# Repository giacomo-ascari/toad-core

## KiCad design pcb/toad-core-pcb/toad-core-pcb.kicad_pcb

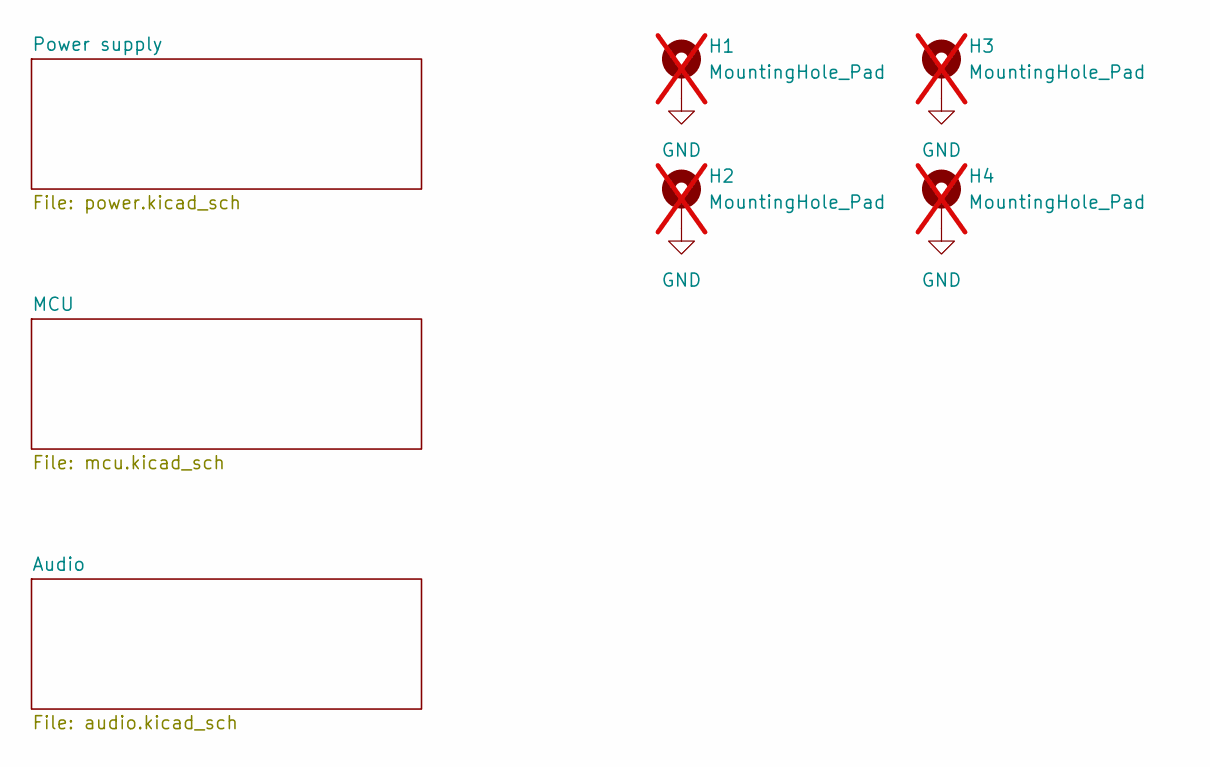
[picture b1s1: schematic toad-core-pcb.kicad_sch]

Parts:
H1, H2, H3, H4: MountingHole_Pad; MountingHole_3.2mm_M3_ISO14580_Pad; not fitted

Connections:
GND: H1.1 (1_1), H2.1 (1_1), H3.1 (1_1), H4.1 (1_1); also elsewhere on the board

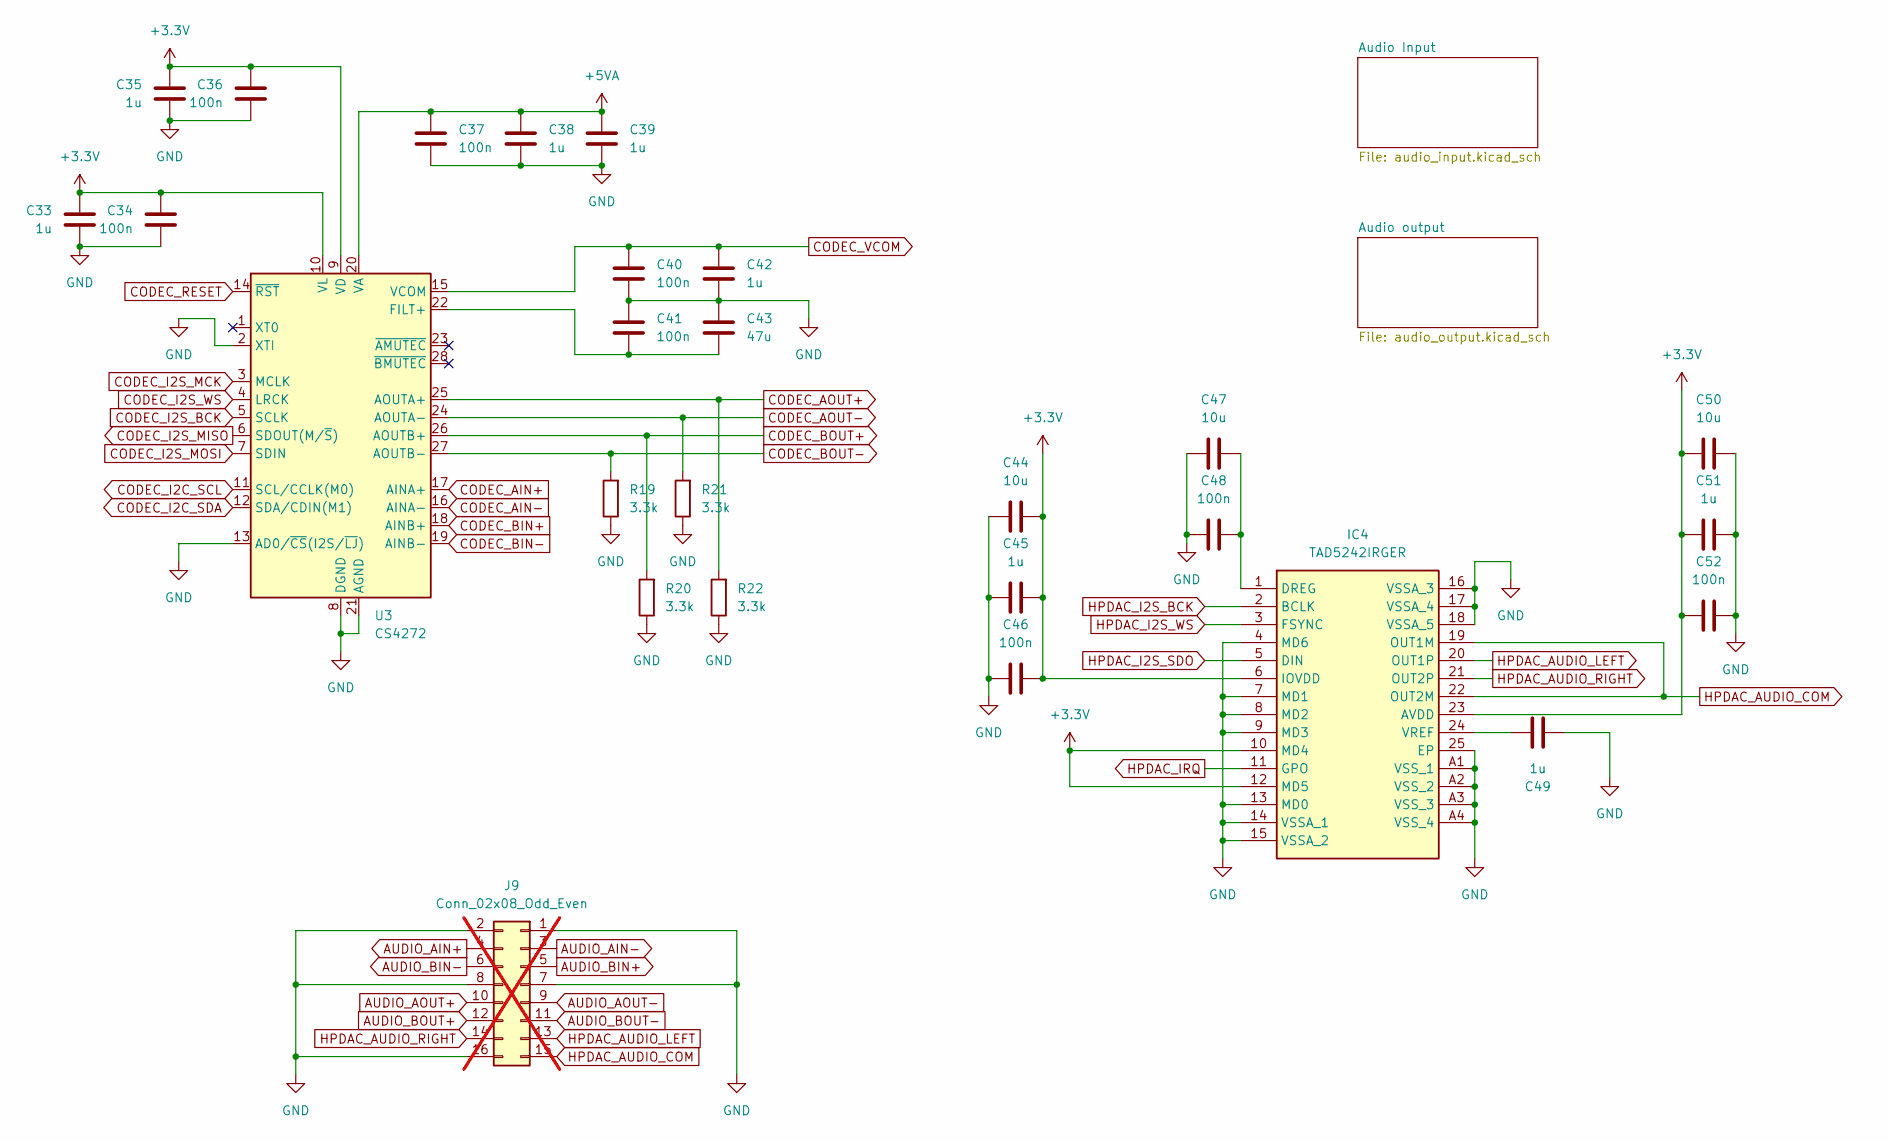
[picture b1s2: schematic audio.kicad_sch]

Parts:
C33, C35, C38, C39, C42, C45, C49, C51: 1u; C_0603_1608Metric; JLCPCB Part # C15849
C34, C36, C37, C40, C41, C46, C48, C52: 100n; C_0603_1608Metric; JLCPCB Part # C14663
C43: 47u; C_0805_2012Metric; JLCPCB Part # C16780
C44, C47, C50: 10u; C_0805_2012Metric; JLCPCB Part # C440198
IC4: TAD5242IRGER; Manufacturer_Part_Number TAD5242IRGER; Mouser Part Number 595-TAD5242IRGER
J9: Conn_02x08_Odd_Even; PinHeader_2x08_P2.54mm_Vertical; not fitted
R19, R20, R21, R22: 3.3k; R_0603_1608Metric; JLCPCB Part # C22978
U3: CS4272; TSSOP-28_4.4x9.7mm_P0.65mm; JLCPCB Part # C2151111

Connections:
+3.3V: C33.1, C34.1, C35.1, C36.1, C44.1, C45.1, C46.1, C50.1, C51.1, C52.1, IC4.6 (IOVDD), IC4.10 (MD4), IC4.12 (MD5), IC4.23 (AVDD), U3.9 (VD), U3.10 (VL); also elsewhere on the board
+5VA: C37.1, C38.1, C39.1, U3.20 (VA); also elsewhere on the board
AUDIO_AIN+: J9.4; also elsewhere on the board
AUDIO_AIN-: J9.3; also elsewhere on the board
AUDIO_AOUT+: J9.10; also elsewhere on the board
AUDIO_AOUT-: J9.9; also elsewhere on the board
AUDIO_BIN+: J9.5; also elsewhere on the board
AUDIO_BIN-: J9.6; also elsewhere on the board
AUDIO_BOUT+: J9.12; also elsewhere on the board
AUDIO_BOUT-: J9.11; also elsewhere on the board
CODEC_AIN+: U3.17 (AINA+); also elsewhere on the board
CODEC_AIN-: U3.16 (AINA-); also elsewhere on the board
CODEC_AOUT+: R22.2, U3.25 (AOUTA+); also elsewhere on the board
CODEC_AOUT-: R21.2, U3.24 (AOUTA-); also elsewhere on the board
CODEC_BIN+: U3.18 (AINB+); also elsewhere on the board
CODEC_BIN-: U3.19 (AINB-); also elsewhere on the board
CODEC_BOUT+: R20.2, U3.26 (AOUTB+); also elsewhere on the board
CODEC_BOUT-: R19.2, U3.27 (AOUTB-); also elsewhere on the board
CODEC_I2C_SCL: U3.11 (SCL/CCLK(M0)); also elsewhere on the board
CODEC_I2C_SDA: U3.12 (SDA/CDIN(M1)); also elsewhere on the board
CODEC_I2S_BCK: U3.5 (SCLK); also elsewhere on the board
CODEC_I2S_MCK: U3.3 (MCLK); also elsewhere on the board
CODEC_I2S_MISO: U3.6 (SDOUT(M/~S)); also elsewhere on the board
CODEC_I2S_MOSI: U3.7 (SDIN); also elsewhere on the board
CODEC_I2S_WS: U3.4 (LRCK); also elsewhere on the board
CODEC_RESET: U3.14 (~RST); also elsewhere on the board
CODEC_VCOM: C40.1, C42.1, U3.15 (VCOM); also elsewhere on the board
GND: C33.2, C34.2, C35.2, C36.2, C37.2, C38.2, C39.2, C40.2, C41.1, C42.2, C43.1, C44.2, C45.2, C46.2, C47.2, C48.2, C49.1, C50.2, C51.2, C52.2, IC4.4 (MD6), IC4.7 (MD1), IC4.8 (MD2), IC4.9 (MD3), IC4.13 (MD0), IC4.14 (VSSA_1), IC4.15 (VSSA_2), IC4.16 (VSSA_3), IC4.17 (VSSA_4), IC4.18 (VSSA_5), IC4.25 (EP), IC4.A1 (VSS_1), IC4.A2 (VSS_2), IC4.A3 (VSS_3), IC4.A4 (VSS_4), J9.1, J9.2, J9.7, J9.8, J9.16, R19.1, R20.1, R21.1, R22.1, U3.2 (XTI), U3.8 (DGND), U3.13 (AD0/~CS(I2S/~LJ)), U3.21 (AGND); also elsewhere on the board
HPDAC_AUDIO_COM: IC4.19 (OUT1M), IC4.22 (OUT2M), J9.15
HPDAC_AUDIO_LEFT: IC4.20 (OUT1P), J9.13
HPDAC_AUDIO_RIGHT: IC4.21 (OUT2P), J9.14
HPDAC_I2S_BCK: IC4.2 (BCLK); also elsewhere on the board
HPDAC_I2S_SDO: IC4.5 (DIN); also elsewhere on the board
HPDAC_I2S_WS: IC4.3 (FSYNC); also elsewhere on the board
HPDAC_IRQ: IC4.11 (GPO); also elsewhere on the board
unnamed: C47.1, C48.1, IC4.1 (DREG)
unnamed: C49.2, IC4.24 (VREF)
unnamed: C41.2, C43.2, U3.22 (FILT+)

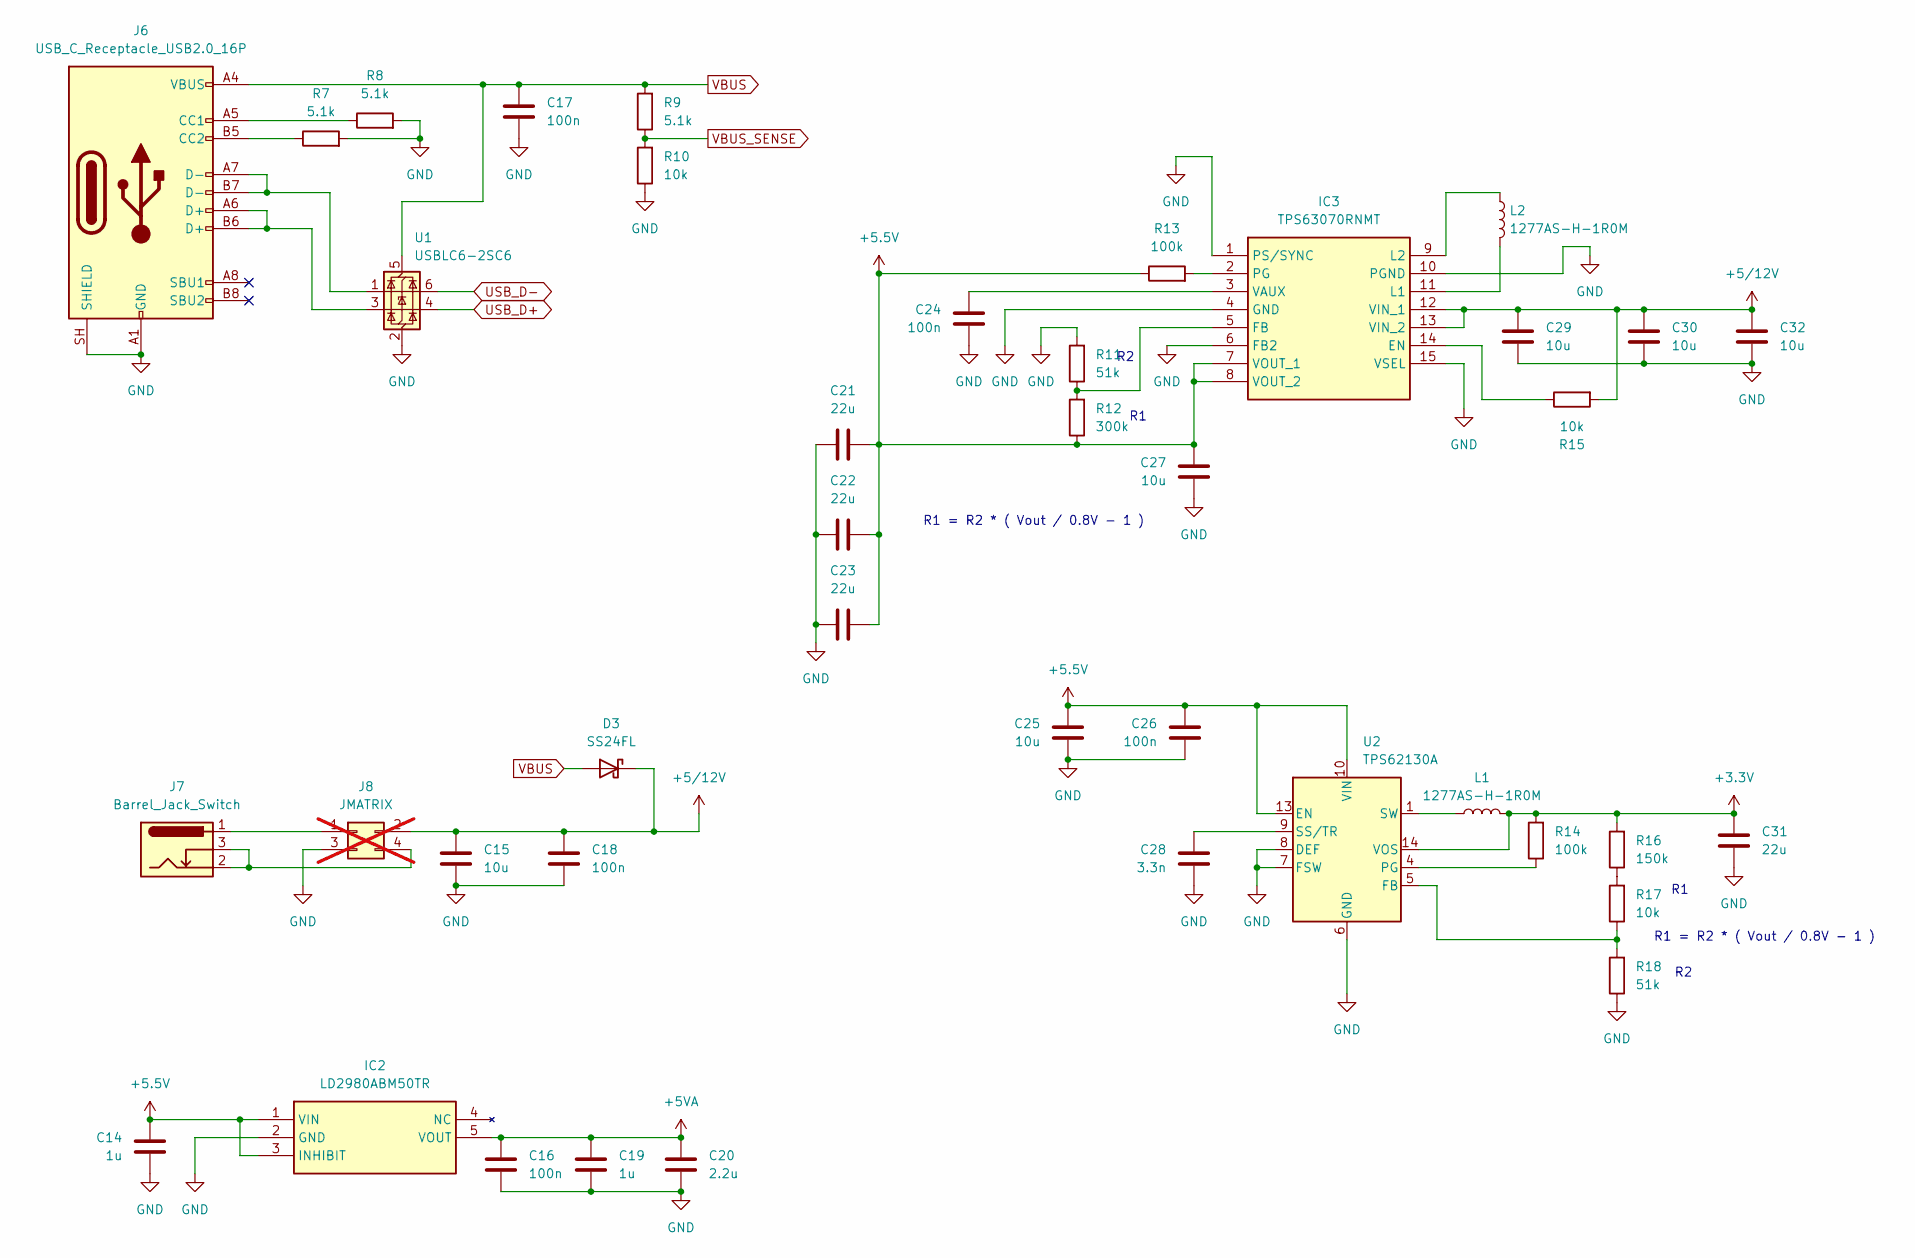
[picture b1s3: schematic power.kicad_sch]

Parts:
C14, C19: 1u; C_0603_1608Metric; JLCPCB Part # C15849
C15, C25, C30, C32: 10u; C_0805_2012Metric; JLCPCB Part # C440198
C16, C17, C18, C24, C26: 100n; C_0603_1608Metric; JLCPCB Part # C14663
C20: 2.2u; C_0603_1608Metric; JLCPCB Part # C23630
C21, C22, C23, C31: 22u; C_0805_2012Metric; JLCPCB Part # C45783
C27, C29: 10u; C_0603_1608Metric; JLCPCB Part # C96446
C28: 3.3n; C_0603_1608Metric; JLCPCB Part # C1613
D3: SS24FL; D_SOD-123F; JLCPCB Part # C894433
IC2: LD2980ABM50TR; SOT95P280X145-5N; Manufacturer_Part_Number LD2980ABM50TR; Mouser Part Number 511-LD2980ABM50
IC3: TPS63070RNMT; TPS630701RNMR; Manufacturer_Part_Number TPS63070RNMT; Mouser Part Number 595-TPS63070RNMT
J6: USB_C_Receptacle_USB2.0_16P; USB_C_Receptacle_GCT_USB4105-xx-A_16P_TopMnt_Horizontal; JLCPCB Part # C3020560
J7: Barrel_Jack_Switch; BarrelJack_Wuerth_6941xx301002; JLCPCB Part # C5441017
J8: JMATRIX; PinHeader_2x02_P2.54mm_Vertical; not fitted
L1, L2: 1277AS-H-1R0M; L_1210_3225Metric; JLCPCB Part # C237284
R7, R8, R9: 5.1k; R_0603_1608Metric; JLCPCB Part # C23186
R10, R15, R17: 10k; R_0603_1608Metric; JLCPCB Part # C25804
R11, R18: 51k; R_0603_1608Metric; JLCPCB Part # C23196
R12: 300k; R_0603_1608Metric; JLCPCB Part # C23024
R13, R14: 100k; R_0603_1608Metric; JLCPCB Part # C25803
R16: 150k; R_0603_1608Metric; JLCPCB Part # C22807
U1: USBLC6-2SC6; SOT-23-6; JLCPCB Part # C7519
U2: TPS62130A; VQFN-16-1EP_3x3mm_P0.5mm_EP1.68x1.68mm_ThermalVias; JLCPCB Part # C2070623

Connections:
+3.3V: C31.1, L1.2, R14.2, R16.2, U2.14 (VOS); also elsewhere on the board
+5.5V: C14.1, C21.2, C22.2, C23.2, C25.1, C26.1, C27.1, IC2.1 (VIN), IC2.3 (INHIBIT), IC3.7 (VOUT_1), IC3.8 (VOUT_2), R12.1, R13.1, U2.10 (VIN), U2.11 (VIN), U2.12 (VIN), U2.13 (EN)
+5VA: C16.1, C19.1, C20.1, IC2.5 (VOUT); also elsewhere on the board
+5/12V: C15.1, C18.1, C29.1, C30.1, C32.1, D3.1 (K), IC3.12 (VIN_1), IC3.13 (VIN_2), J8.2, R15.2
GND: C14.2, C15.2, C16.2, C17.2, C18.2, C19.2, C20.2, C21.1, C22.1, C23.1, C24.2, C25.2, C26.2, C27.2, C28.2, C29.2, C30.2, C31.2, C32.2, IC2.2 (GND), IC3.1 (PS/SYNC), IC3.4 (GND), IC3.6 (FB2), IC3.10 (PGND), IC3.15 (VSEL), J6.A1 (GND), J6.A12 (GND), J6.B1 (GND), J6.B12 (GND), J6.SH (SHIELD), J8.3, R7.2, R8.2, R10.1, R11.2, R18.1, U1.2 (GND), U2.6 (GND), U2.7 (FSW), U2.8 (DEF), U2.15 (GND), U2.16 (GND), U2.17 (GND); also elsewhere on the board
unnamed: IC3.14 (EN), R15.1
unnamed: IC3.5 (FB), R11.1, R12.2
unnamed: IC3.11 (L1), L2.2
unnamed: IC3.9 (L2), L2.1
unnamed: IC3.2 (PG), R13.2
unnamed: C24.1, IC3.3 (VAUX)
unnamed: J6.A5 (CC1), R8.1
unnamed: J6.B5 (CC2), R7.1
unnamed: J6.A6 (D+), J6.B6 (D+), U1.3 (I/O2)
unnamed: J6.A7 (D-), J6.B7 (D-), U1.1 (I/O1)
unnamed: J7.1, J8.1
unnamed: J7.2, J7.3, J8.4
unnamed: L1.1, U2.1 (SW), U2.2 (SW), U2.3 (SW)
unnamed: R16.1, R17.2
unnamed: R17.1, R18.2, U2.5 (FB)
unnamed: R14.1, U2.4 (PG)
unnamed: C28.1, U2.9 (SS/TR)
USB_D+: U1.4 (I/O2); also elsewhere on the board
USB_D-: U1.6 (I/O1); also elsewhere on the board
VBUS: C17.1, D3.2 (A), J6.A4 (VBUS), J6.A9 (VBUS), J6.B4 (VBUS), J6.B9 (VBUS), R9.2, U1.5 (VBUS)
VBUS_SENSE: R9.1, R10.2; also elsewhere on the board

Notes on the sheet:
R1 = R2 * ( Vout / 0.8V - 1 )

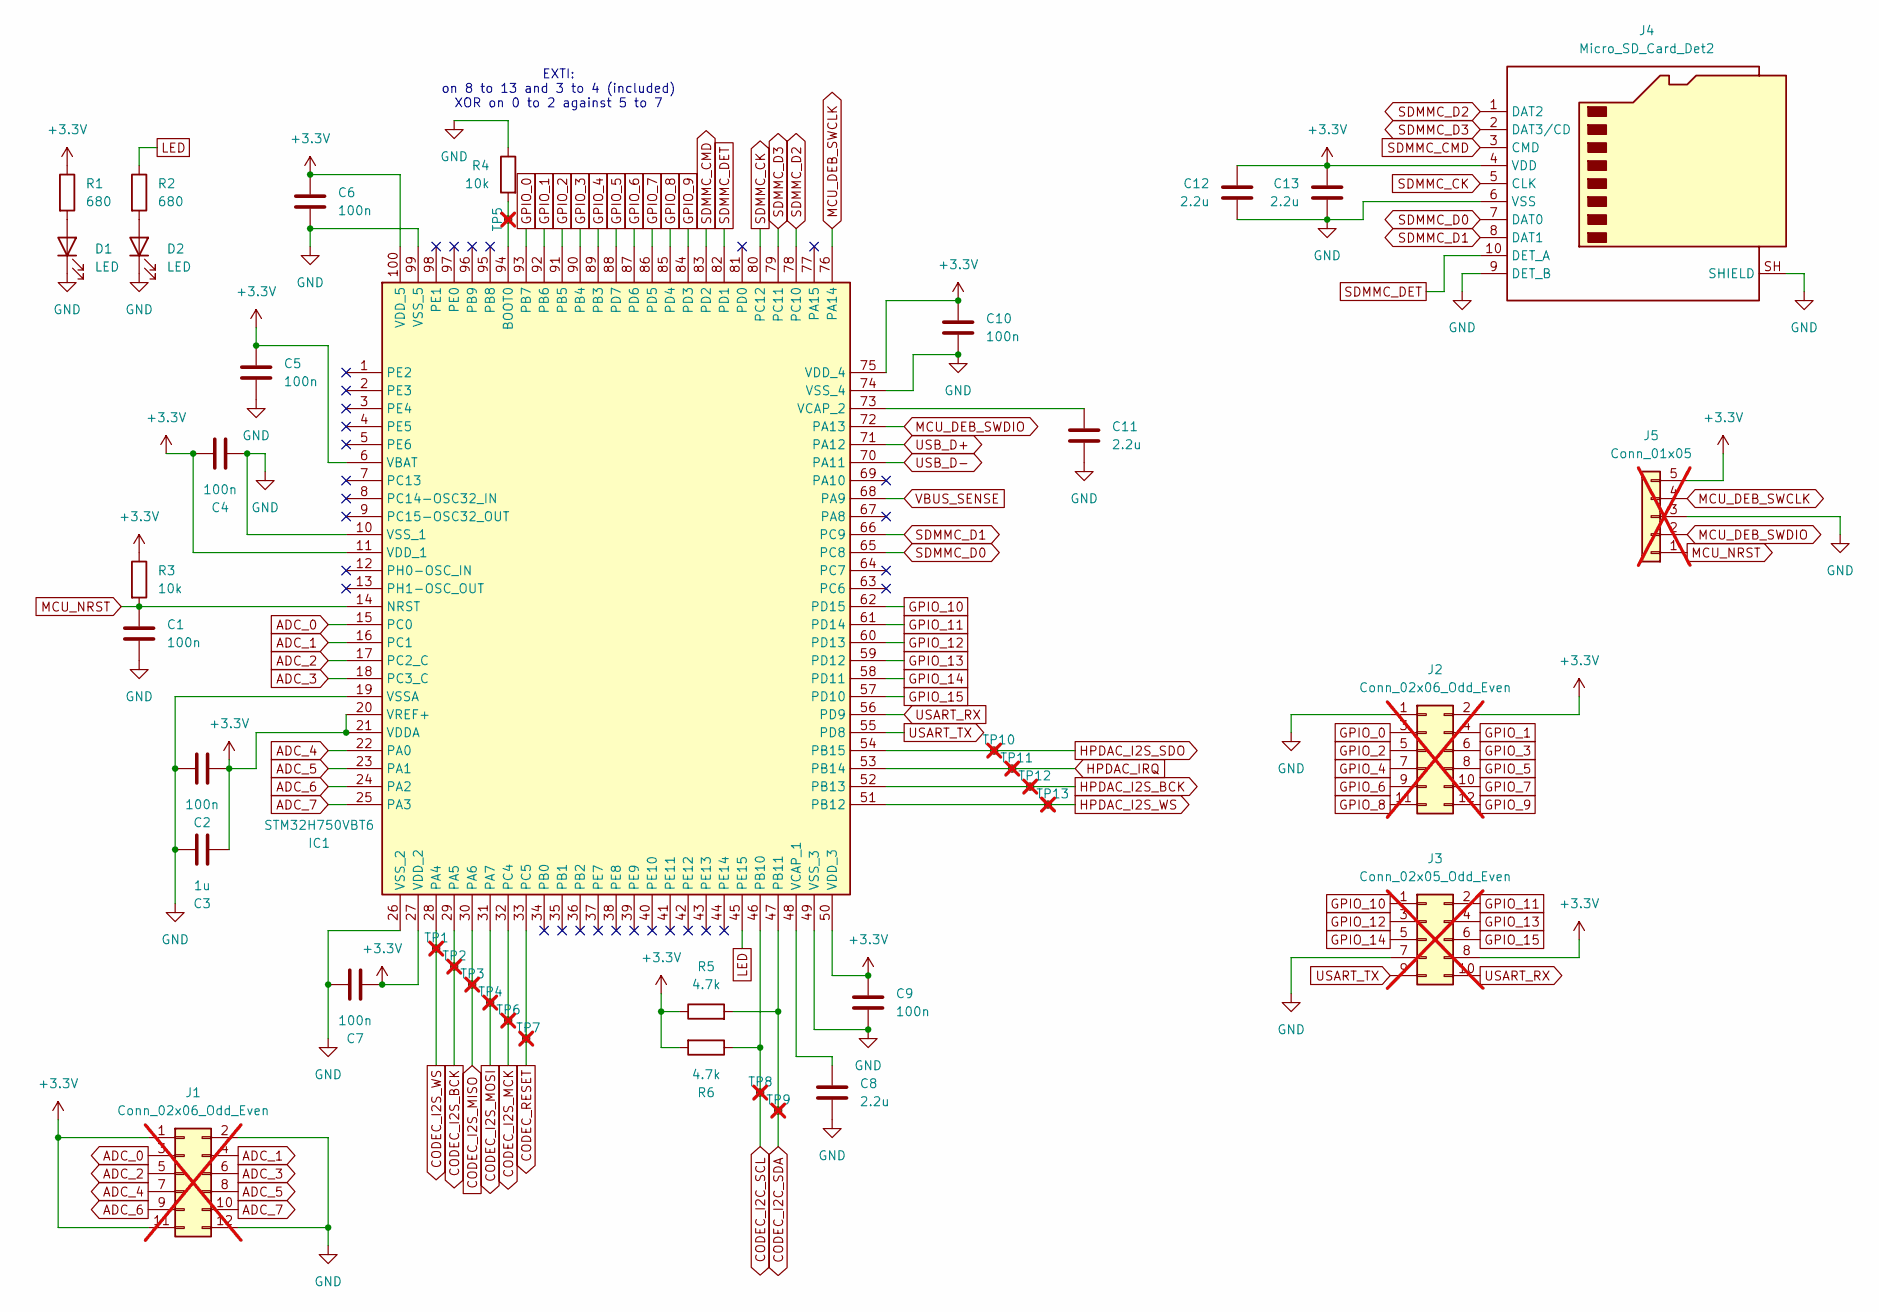
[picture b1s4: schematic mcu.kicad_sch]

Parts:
C1, C2, C4, C5, C6, C7, C9, C10: 100n; C_0603_1608Metric; JLCPCB Part # C14663
C3: 1u; C_0603_1608Metric; JLCPCB Part # C15849
C8, C11, C12, C13: 2.2u; C_0603_1608Metric; JLCPCB Part # C23630
D1, D2: LED; LED_0603_1608Metric; JLCPCB Part # C2286
IC1: STM32H750VBT6; QFP50P1600X1600X160-100N; Manufacturer_Part_Number STM32H750VBT6; Mouser Part Number 511-STM32H750VBT6
J1, J2: Conn_02x06_Odd_Even; PinHeader_2x06_P2.54mm_Vertical; not fitted
J3: Conn_02x05_Odd_Even; PinHeader_2x05_P2.54mm_Vertical; not fitted
J4: Micro_SD_Card_Det2; microSD_HC_Molex_104031-0811; JLCPCB Part # C585350
J5: Conn_01x05; JST_PH_B5B-PH-K_1x05_P2.00mm_Vertical; not fitted
R1, R2: 680; R_0603_1608Metric; JLCPCB Part # C23228
R3, R4: 10k; R_0603_1608Metric; JLCPCB Part # C25804
R5, R6: 4.7k; R_0603_1608Metric; JLCPCB Part # C23162
TP1, TP2, TP3, TP4, TP5, TP6, TP7, TP8, TP9, TP10, TP11, TP12, TP13: TestPoint_Small; custom_d0.6; not fitted

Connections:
+3.3V: C2.1, C3.1, C4.2, C5.1, C6.1, C7.1, C9.1, C10.1, C12.1, C13.1, IC1.6 (VBAT), IC1.11 (VDD_1), IC1.20 (VREF+), IC1.21 (VDDA), IC1.27 (VDD_2), IC1.50 (VDD_3), IC1.75 (VDD_4), IC1.100 (VDD_5), J1.1, J1.11, J2.2, J3.8, J4.4 (VDD), J5.5, R1.1, R3.1, R5.1, R6.2; also elsewhere on the board
ADC_0: IC1.15 (PC0), J1.3
ADC_1: IC1.16 (PC1), J1.4
ADC_2: IC1.17 (PC2_C), J1.5
ADC_3: IC1.18 (PC3_C), J1.6
ADC_4: IC1.22 (PA0), J1.7
ADC_5: IC1.23 (PA1), J1.8
ADC_6: IC1.24 (PA2), J1.9
ADC_7: IC1.25 (PA3), J1.10
CODEC_I2C_SCL: IC1.46 (PB10), R6.1, TP8.1 (1_1); also elsewhere on the board
CODEC_I2C_SDA: IC1.47 (PB11), R5.2, TP9.1 (1_1); also elsewhere on the board
CODEC_I2S_BCK: IC1.29 (PA5), TP2.1 (1_1); also elsewhere on the board
CODEC_I2S_MCK: IC1.32 (PC4), TP6.1 (1_1); also elsewhere on the board
CODEC_I2S_MISO: IC1.30 (PA6), TP3.1 (1_1); also elsewhere on the board
CODEC_I2S_MOSI: IC1.31 (PA7), TP4.1 (1_1); also elsewhere on the board
CODEC_I2S_WS: IC1.28 (PA4), TP1.1 (1_1); also elsewhere on the board
CODEC_RESET: IC1.33 (PC5), TP7.1 (1_1); also elsewhere on the board
GND: C1.2, C2.2, C3.2, C4.1, C5.2, C6.2, C7.2, C8.2, C9.2, C10.2, C11.2, C12.2, C13.2, D1.1 (K), D2.1 (K), IC1.10 (VSS_1), IC1.19 (VSSA), IC1.26 (VSS_2), IC1.49 (VSS_3), IC1.74 (VSS_4), IC1.99 (VSS_5), J1.2, J1.12, J2.1, J3.7, J4.6 (VSS), J4.9 (DET_B), J4.SH (SHIELD), J5.3, R4.1; also elsewhere on the board
GPIO_0: IC1.93 (PB7), J2.3
GPIO_1: IC1.92 (PB6), J2.4
GPIO_2: IC1.91 (PB5), J2.5
GPIO_3: IC1.90 (PB4), J2.6
GPIO_4: IC1.89 (PB3), J2.7
GPIO_5: IC1.88 (PD7), J2.8
GPIO_6: IC1.87 (PD6), J2.9
GPIO_7: IC1.86 (PD5), J2.10
GPIO_8: IC1.85 (PD4), J2.11
GPIO_9: IC1.84 (PD3), J2.12
GPIO_10: IC1.62 (PD15), J3.1
GPIO_11: IC1.61 (PD14), J3.2
GPIO_12: IC1.60 (PD13), J3.3
GPIO_13: IC1.59 (PD12), J3.4
GPIO_14: IC1.58 (PD11), J3.5
GPIO_15: IC1.57 (PD10), J3.6
HPDAC_I2S_BCK: IC1.52 (PB13), TP12.1 (1_1); also elsewhere on the board
HPDAC_I2S_SDO: IC1.54 (PB15), TP10.1 (1_1); also elsewhere on the board
HPDAC_I2S_WS: IC1.51 (PB12), TP13.1 (1_1); also elsewhere on the board
HPDAC_IRQ: IC1.53 (PB14), TP11.1 (1_1); also elsewhere on the board
LED: IC1.45 (PE15), R2.1
MCU_DEB_SWCLK: IC1.76 (PA14), J5.4
MCU_DEB_SWDIO: IC1.72 (PA13), J5.2
MCU_NRST: C1.1, IC1.14 (NRST), J5.1, R3.2
unnamed: D1.2 (A), R1.2
unnamed: D2.2 (A), R2.2
unnamed: IC1.94 (BOOT0), R4.2, TP5.1 (1_1)
unnamed: C8.1, IC1.48 (VCAP_1)
unnamed: C11.1, IC1.73 (VCAP_2)
SDMMC_CK: IC1.80 (PC12), J4.5 (CLK)
SDMMC_CMD: IC1.83 (PD2), J4.3 (CMD)
SDMMC_D0: IC1.65 (PC8), J4.7 (DAT0)
SDMMC_D1: IC1.66 (PC9), J4.8 (DAT1)
SDMMC_D2: IC1.78 (PC10), J4.1 (DAT2)
SDMMC_D3: IC1.79 (PC11), J4.2 (DAT3/CD)
SDMMC_DET: IC1.82 (PD1), J4.10 (DET_A)
USART_RX: IC1.56 (PD9), J3.10
USART_TX: IC1.55 (PD8), J3.9
USB_D+: IC1.71 (PA12); also elsewhere on the board
USB_D-: IC1.70 (PA11); also elsewhere on the board
VBUS_SENSE: IC1.68 (PA9); also elsewhere on the board

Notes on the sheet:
EXTI: on 8 to 13 and 3 to 4 (included) XOR on 0 to 2 against 5 to 7

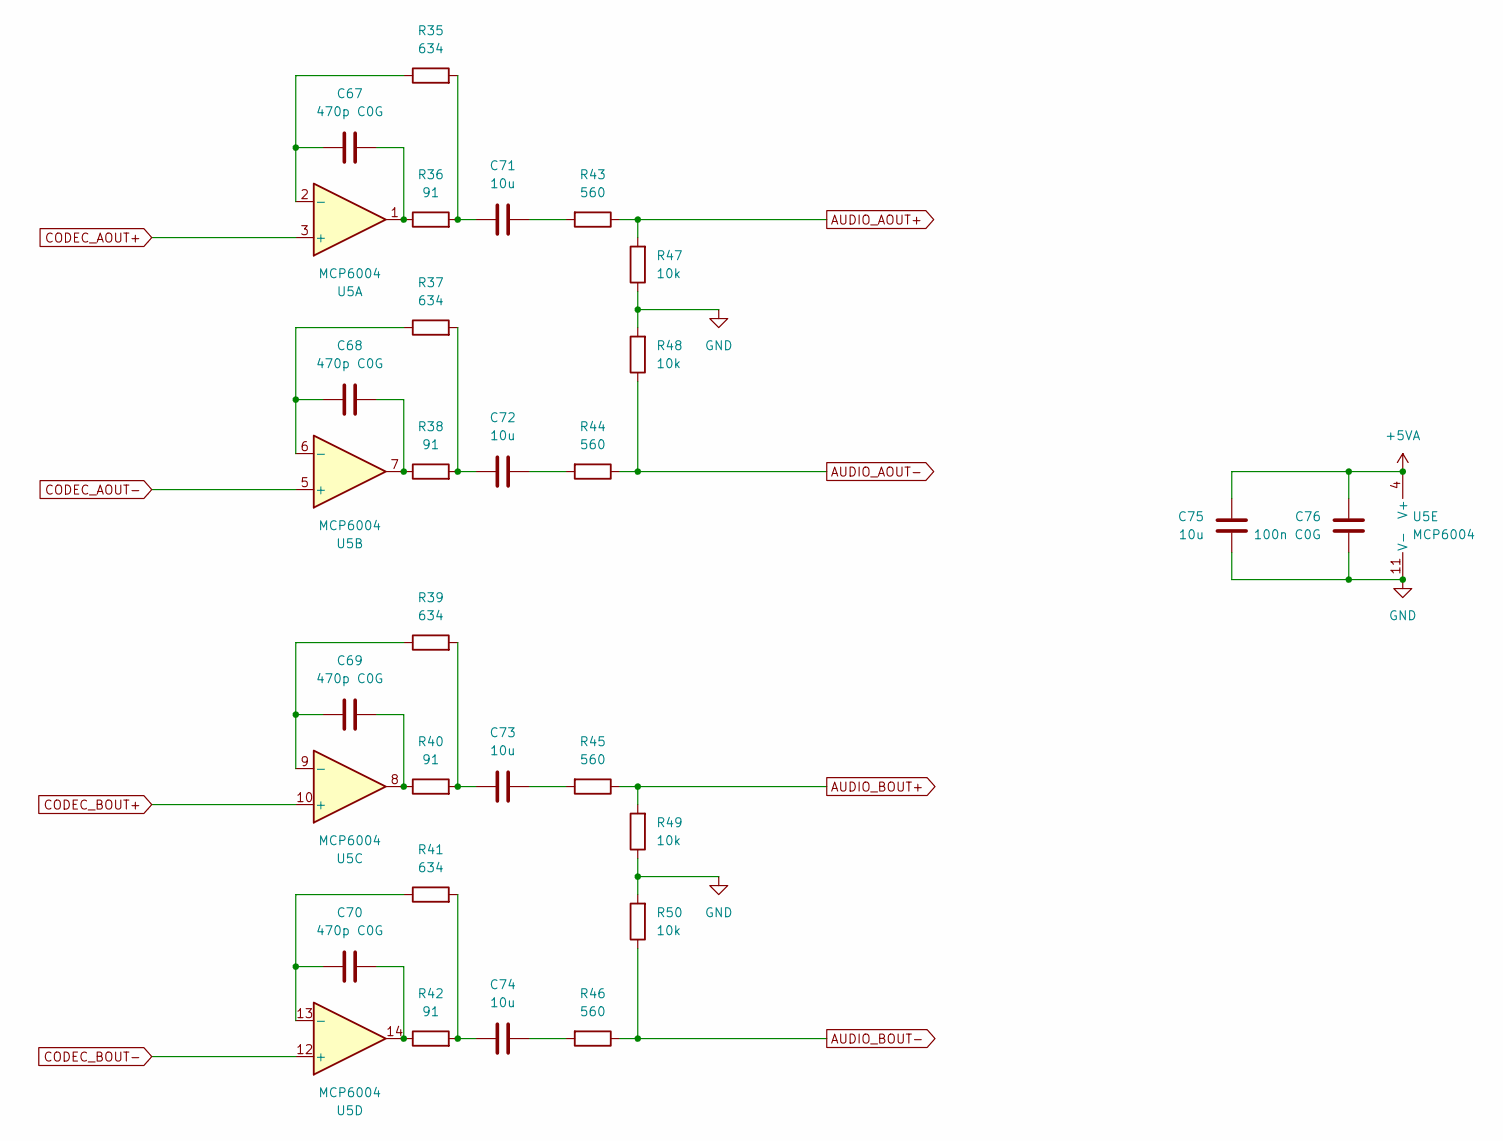
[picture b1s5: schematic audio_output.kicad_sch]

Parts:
C67, C68, C69, C70: 470p C0G; C_0603_1608Metric; JLCPCB Part # C437459
C71, C72, C73, C74, C75: 10u; C_0805_2012Metric; JLCPCB Part # C440198
C76: 100n C0G; C_0603_1608Metric; JLCPCB Part # C14663
R35, R37, R39, R41: 634; R_0603_1608Metric; JLCPCB Part # C2079726
R36, R38, R40, R42: 91; R_0603_1608Metric; JLCPCB Part # C25199
R43, R44, R45, R46: 560; R_0603_1608Metric; JLCPCB Part # C23204
R47, R48, R49, R50: 10k; R_0603_1608Metric; JLCPCB Part # C25804
U5: MCP6004; TSSOP-14_4.4x5mm_P0.65mm; JLCPCB Part # C50282

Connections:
+5VA: C75.1, C76.1, U5.4 (V+); also elsewhere on the board
AUDIO_AOUT+: R43.1, R47.2; also elsewhere on the board
AUDIO_AOUT-: R44.1, R48.1; also elsewhere on the board
AUDIO_BOUT+: R45.1, R49.2; also elsewhere on the board
AUDIO_BOUT-: R46.1, R50.1; also elsewhere on the board
CODEC_AOUT+: U5.3 (+); also elsewhere on the board
CODEC_AOUT-: U5.5 (+); also elsewhere on the board
CODEC_BOUT+: U5.10 (+); also elsewhere on the board
CODEC_BOUT-: U5.12 (+); also elsewhere on the board
GND: C75.2, C76.2, R47.1, R48.2, R49.1, R50.2, U5.11 (V-); also elsewhere on the board
unnamed: C67.1, R36.1, U5.1
unnamed: C68.1, R38.1, U5.7
unnamed: C69.1, R40.1, U5.8
unnamed: C70.1, R42.1, U5.14
unnamed: C71.1, R43.2
unnamed: C71.2, R35.2, R36.2
unnamed: C72.1, R44.2
unnamed: C72.2, R37.2, R38.2
unnamed: C73.1, R45.2
unnamed: C73.2, R39.2, R40.2
unnamed: C74.1, R46.2
unnamed: C74.2, R41.2, R42.2
unnamed: C67.2, R35.1, U5.2 (-)
unnamed: C68.2, R37.1, U5.6 (-)
unnamed: C69.2, R39.1, U5.9 (-)
unnamed: C70.2, R41.1, U5.13 (-)

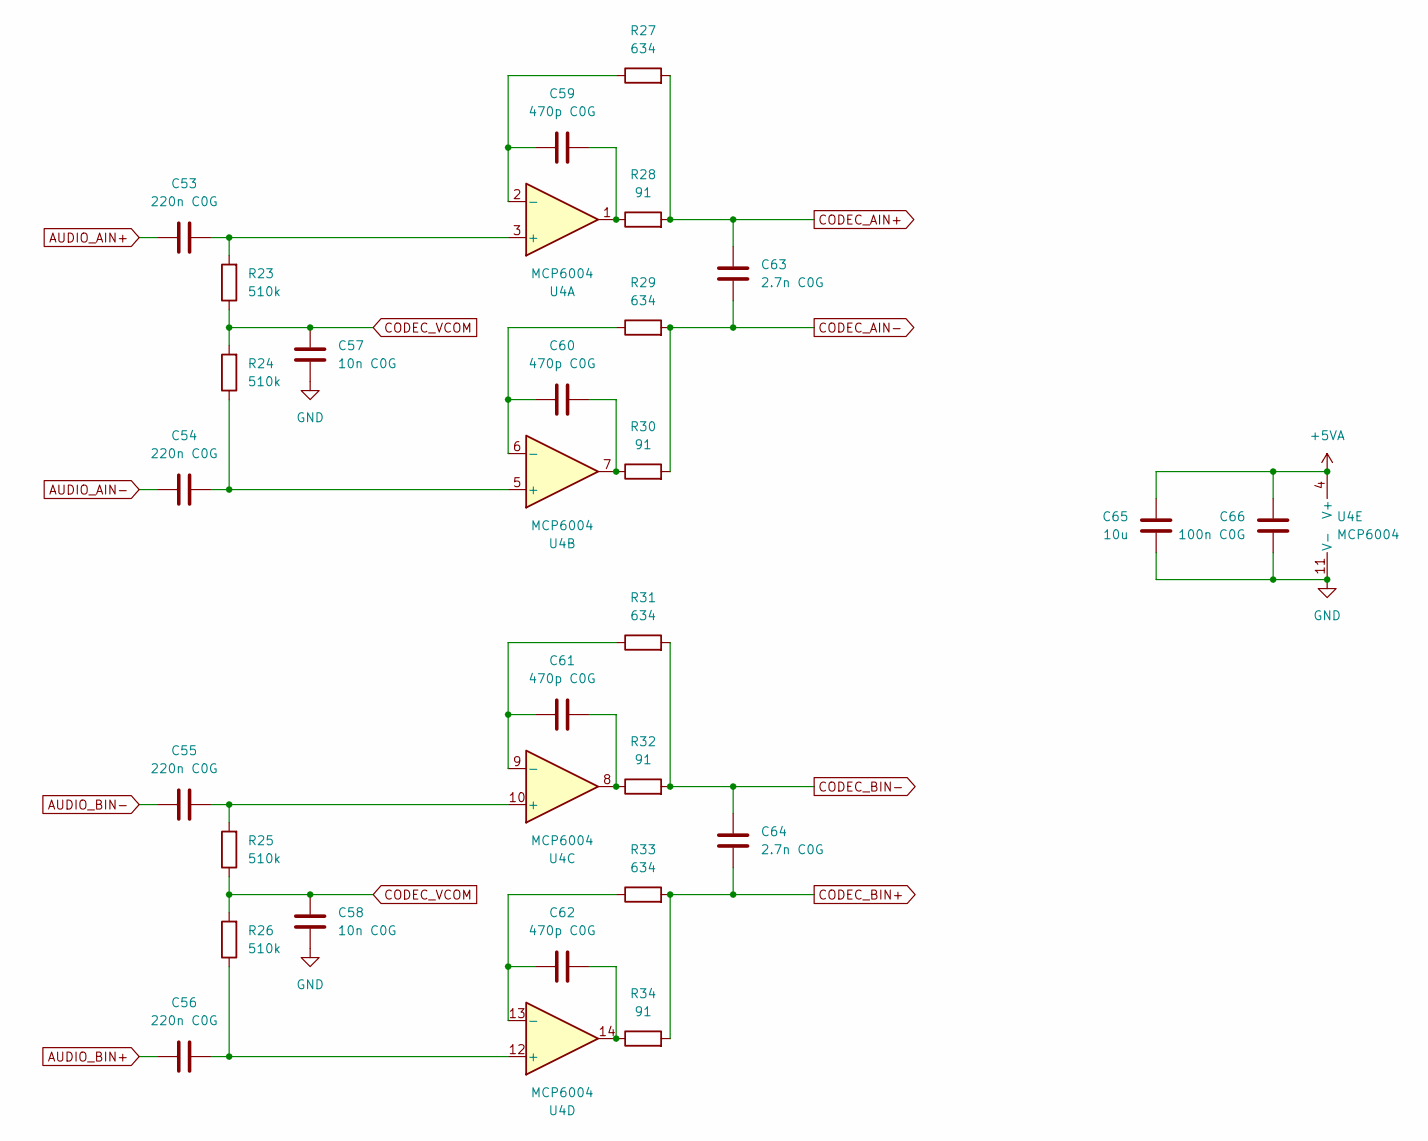
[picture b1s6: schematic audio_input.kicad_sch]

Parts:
C53, C54, C55, C56: 220n C0G; C_0603_1608Metric; JLCPCB Part # C21120
C57, C58: 10n C0G; C_0603_1608Metric; JLCPCB Part # C307500
C59, C60, C61, C62: 470p C0G; C_0603_1608Metric; JLCPCB Part # C437459
C63, C64: 2.7n C0G; C_0603_1608Metric; JLCPCB Part # C1625600
C65: 10u; C_0805_2012Metric; JLCPCB Part # C440198
C66: 100n C0G; C_0603_1608Metric; JLCPCB Part # C14663
R23, R24, R25, R26: 510k; R_0603_1608Metric; JLCPCB Part # C23192
R27, R29, R31, R33: 634; R_0603_1608Metric; JLCPCB Part # C2079726
R28, R30, R32, R34: 91; R_0603_1608Metric; JLCPCB Part # C25199
U4: MCP6004; TSSOP-14_4.4x5mm_P0.65mm; JLCPCB Part # C50282

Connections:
+5VA: C65.1, C66.1, U4.4 (V+); also elsewhere on the board
AUDIO_AIN+: C53.2; also elsewhere on the board
AUDIO_AIN-: C54.2; also elsewhere on the board
AUDIO_BIN+: C56.2; also elsewhere on the board
AUDIO_BIN-: C55.2; also elsewhere on the board
CODEC_AIN+: C63.1, R27.2, R28.2; also elsewhere on the board
CODEC_AIN-: C63.2, R29.2, R30.2; also elsewhere on the board
CODEC_BIN+: C64.2, R33.2, R34.2; also elsewhere on the board
CODEC_BIN-: C64.1, R31.2, R32.2; also elsewhere on the board
CODEC_VCOM: C57.1, C58.1, R23.1, R24.2, R25.1, R26.2; also elsewhere on the board
GND: C57.2, C58.2, C65.2, C66.2, U4.11 (V-); also elsewhere on the board
unnamed: C59.1, R28.1, U4.1
unnamed: C60.1, R30.1, U4.7
unnamed: C61.1, R32.1, U4.8
unnamed: C62.1, R34.1, U4.14
unnamed: C53.1, R23.2, U4.3 (+)
unnamed: C59.2, R27.1, U4.2 (-)
unnamed: C54.1, R24.1, U4.5 (+)
unnamed: C60.2, R29.1, U4.6 (-)
unnamed: C55.1, R25.2, U4.10 (+)
unnamed: C61.2, R31.1, U4.9 (-)
unnamed: C56.1, R26.1, U4.12 (+)
unnamed: C62.2, R33.1, U4.13 (-)

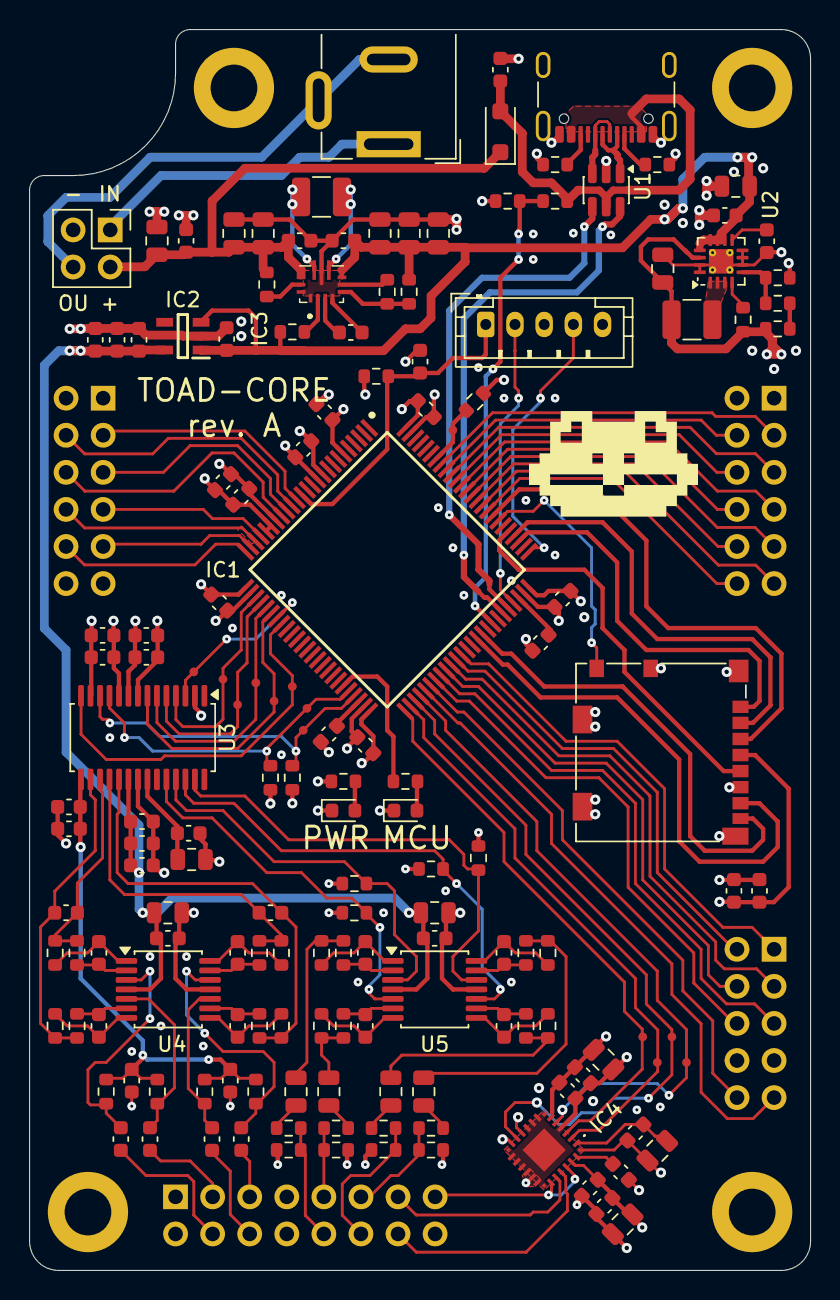
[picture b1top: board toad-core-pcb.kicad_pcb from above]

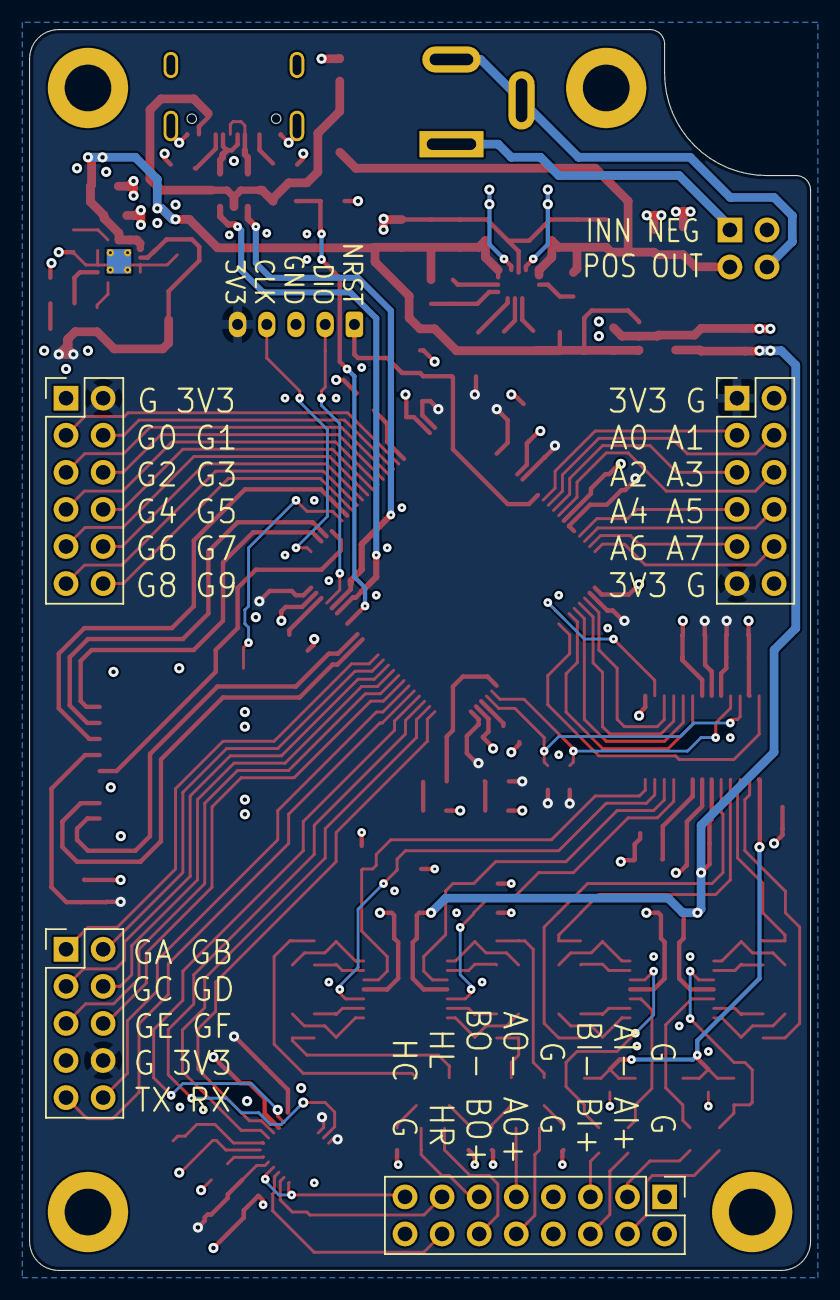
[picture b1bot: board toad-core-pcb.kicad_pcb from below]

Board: 4 copper layers, 53.5 x 85.0 mm, 166 parts (4 on the bottom side), 131 nets.

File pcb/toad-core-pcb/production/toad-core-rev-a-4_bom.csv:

Designator,Footprint,Quantity,Value,LCSC Part #
"C1, C10, C16, C17, C18, C2, C24, C26, C34, C36, C37, C4, C40, C41, C46, C48, C5, C52, C6, C7, C9",0603,21,100n,C14663
"C11, C12, C13, C20, C8",0603,5,2.2u,C23630
"C14, C19, C3, C33, C35, C38, C39, C42, C45, C49, C51",0603,11,1u,C15849
"C15, C25, C30, C32, C44, C47, C50, C65, C71, C72, C73, C74, C75",0805,13,10u,C440198
"C21, C22, C23, C31",0805,4,22u,C45783
"C27, C29",0603,2,10u,C96446
C28,0603,1,3.3n,C1613
C43,0805,1,47u,C16780
"C53, C54, C55, C56",0603,4,220n C0G,C21120
"C57, C58",0603,2,10n C0G,C85973
"C59, C60, C61, C62, C67, C68, C69, C70",0603,8,470p C0G,C437459
"C63, C64",0603,2,2.7n C0G,C1625600
"C66, C76",0603,2,100n C0G,C14663
"D1, D2",0603,2,LED,C2286
D3,D_SOD-123F,1,SS24FL,C894433
IC1,QFP50P1600X1600X160-100N,1,STM32H750VBT6,C404010
IC2,SOT95P280X145-5N,1,LD2980ABM50TR,C411396
IC3,TPS630701RNMR,1,TPS63070RNMT,C964639
IC4,TAD5242IRGER,1,TAD5242IRGER,C42414591
J4,microSD_HC_Molex_104031-0811,1,Micro_SD_Card_Det2,C585350
J6,USB_C_Receptacle_GCT_USB4105-xx-A_16P_TopMnt_Horizontal,1,USB_C_Receptacle_USB2.0_16P,C3020560
J7,BarrelJack_Wuerth_6941xx301002,1,Barrel_Jack_Switch,C5441017
"L1, L2",1210,2,1277AS-H-1R0M,C237284
"R1, R2",0603,2,680,C23228
"R10, R15, R17, R3, R4, R47, R48, R49, R50",0603,9,10k,C25804
"R11, R18",0603,2,51k,C23196
R12,0603,1,300k,C23024
"R13, R14",0603,2,100k,C25803
R16,0603,1,150k,C22807
"R19, R20, R21, R22",0603,4,3.3k,C22978
"R23, R24, R25, R26",0603,4,510k,C23192
"R27, R29, R31, R33, R35, R37, R39, R41",0603,8,634,C2079726
"R28, R30, R32, R34, R36, R38, R40, R42",0603,8,91,C25199
"R43, R44, R45, R46",0603,4,560,C23204
"R5, R6",0603,2,4.7k,C23162
"R7, R8, R9",0603,3,5.1k,C23186
U1,SOT-23-6,1,USBLC6-2SC6,C7519
U2,VQFN-16-1EP_3x3mm_P0.5mm_EP1.68x1.68mm_ThermalVias,1,TPS62130A,C2070623
U3,TSSOP-28_4.4x9.7mm_P0.65mm,1,CS4272,C2151111
"U4, U5",TSSOP-14_4.4x5mm_P0.65mm,2,MCP6004,C50282
